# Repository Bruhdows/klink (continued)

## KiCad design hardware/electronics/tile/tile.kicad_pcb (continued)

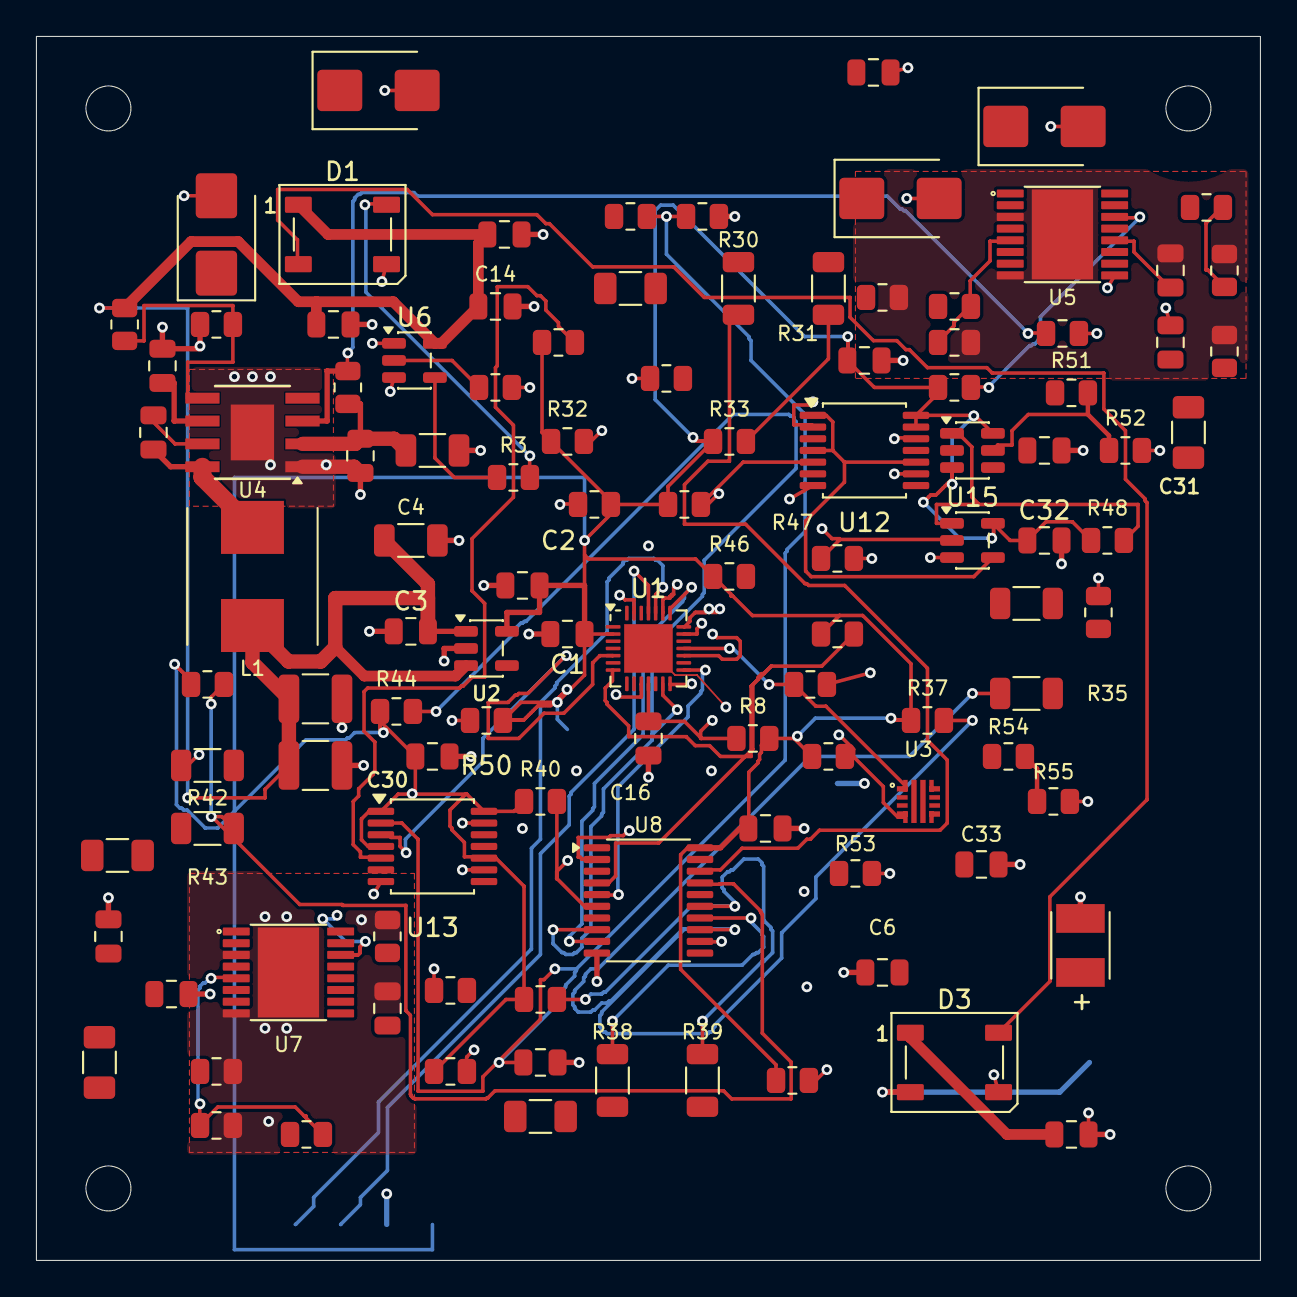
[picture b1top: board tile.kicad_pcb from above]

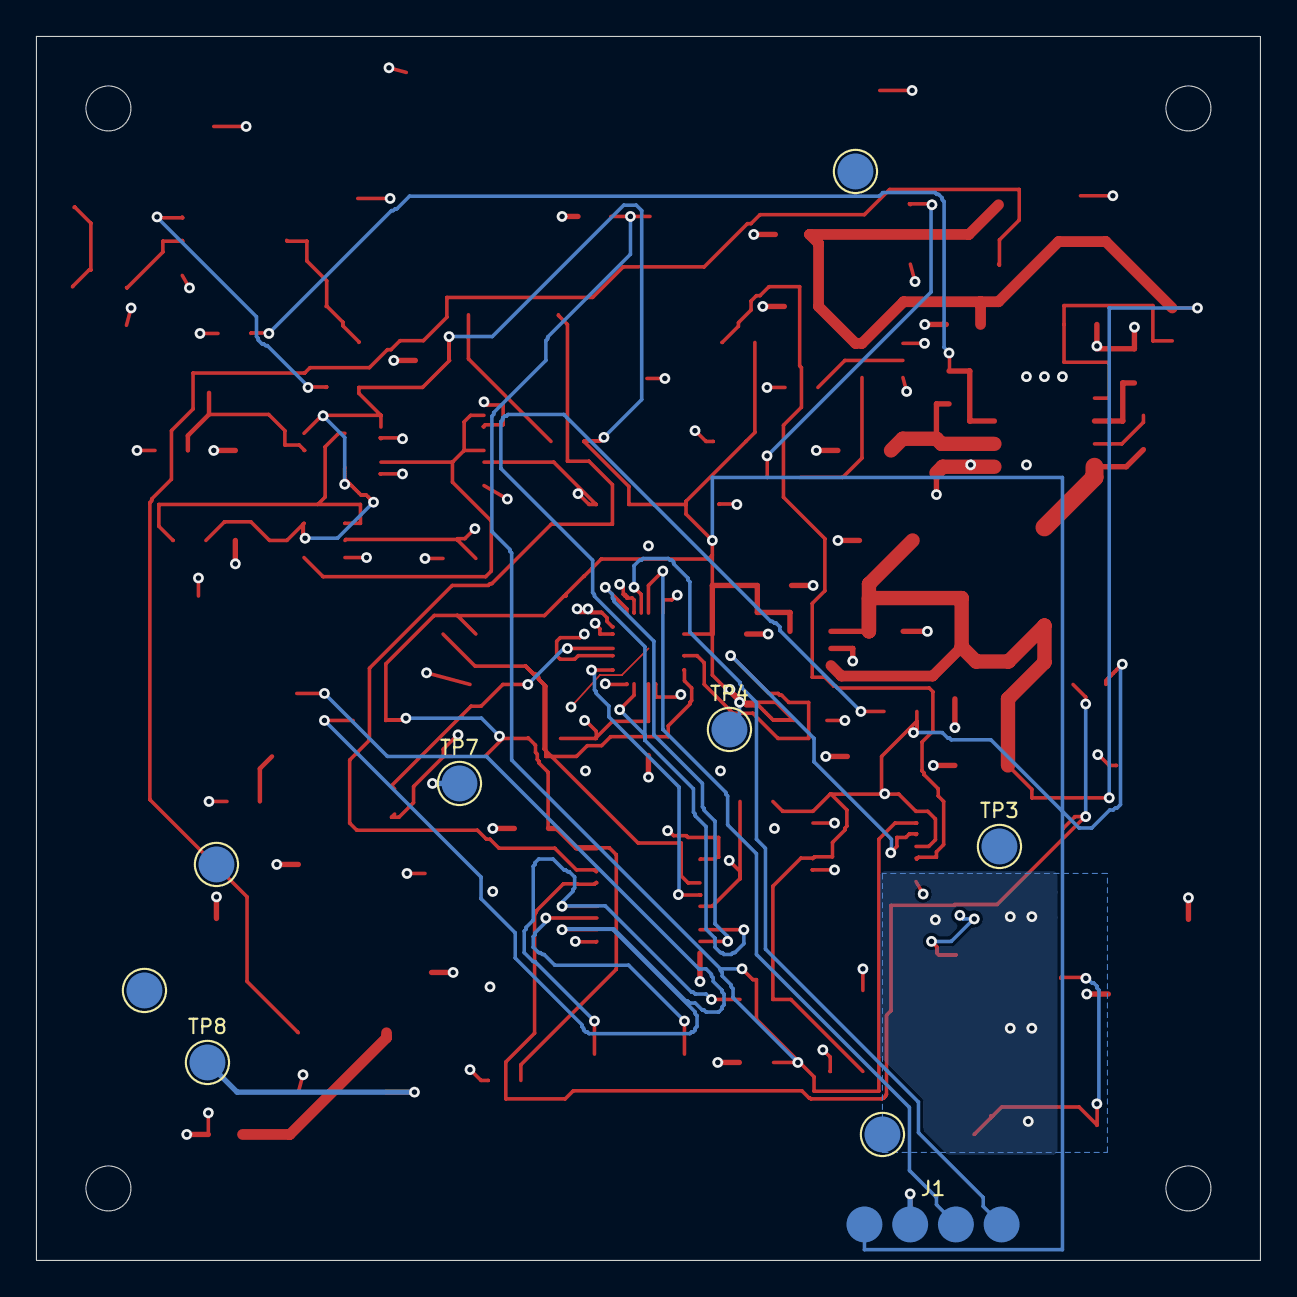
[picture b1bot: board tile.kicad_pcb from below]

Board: 4 copper layers, 68.0 x 68.0 mm, 122 parts (9 on the bottom side), 70 nets.

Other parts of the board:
H1, H2, H3, H4: MountingHole_2.5mm

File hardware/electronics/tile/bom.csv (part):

reference,value,manufacturer_part_number,lcsc_reference,qty_per_tile,qty_for_20_tiles,footprint,purchase_url,unit_price,currency,stock_status,verification_status,qty_for_16_tiles,qty_for_32_tiles,price_status,checked_date
C1,100nF 50V X7R,C2012X7R1H104K125AE,,1,20,Capacitor_SMD:C_0805_2012Metric,https://www.mouser.com/ProductDetail/TDK/C2012X7R1H104K125AE,0.1,USD,,manufacturer data selection; assembly and electrical qualification pending,16,32,engineering allowance; NOT a verified supplier price,
C2,4.7uF,C2012X7R1C475K125AB,,1,20,Capacitor_SMD:C_0805_2012Metric,https://www.mouser.com/ProductDetail/TDK/C2012X7R1C475K125AB,0.1,USD,,manufacturer data selection; assembly and electrical qualification pending,16,32,engineering allowance; NOT a verified supplier price,
C3,1uF,C2012X7R1H105K125AB,,1,20,Capacitor_SMD:C_0805_2012Metric,https://www.mouser.com/ProductDetail/TDK/C2012X7R1H105K125AB,0.1,USD,,manufacturer data selection; assembly and electrical qualification pending,16,32,engineering allowance; NOT a verified supplier price,
C4,10µF,C3216X7R1C106K160AC,,1,20,Capacitor_SMD:C_1206_3216Metric,https://www.mouser.com/ProductDetail/TDK/C3216X7R1C106K160AC,0.35,USD,,manufacturer data selection; assembly and electrical qualification pending,16,32,engineering allowance; NOT a verified supplier price,
C5,100nF 50V X7R,C2012X7R1H104K125AE,,1,20,Capacitor_SMD:C_0805_2012Metric,https://www.mouser.com/ProductDetail/TDK/C2012X7R1H104K125AE,0.1,USD,,manufacturer data selection; assembly and electrical qualification pending,16,32,engineering allowance; NOT a verified supplier price,
C6,100nF 50V X7R,C2012X7R1H104K125AE,,1,20,Capacitor_SMD:C_0805_2012Metric,https://www.mouser.com/ProductDetail/TDK/C2012X7R1H104K125AE,0.1,USD,,manufacturer data selection; assembly and electrical qualification pending,16,32,engineering allowance; NOT a verified supplier price,
C7,120uF 6.3V,6TPE120MAZB,,1,20,Klink:CP_Panasonic_POSCAP_B2,https://www.mouser.com/ProductDetail/Panasonic/6TPE120MAZB,1.2,USD,not procurement-confirmed,datasheet-reviewed design selection; physical qualification pending; do not use above 85C at full 5V-rail tolerance,16,32,engineering allowance; NOT a verified supplier price,
C8,10uF 50V X7R,C3216X7R1H106K160AC,,1,20,Capacitor_SMD:C_1206_3216Metric,https://www.mouser.com/ProductDetail/TDK/C3216X7R1H106K160AC,0.35,USD,,manufacturer data selection; assembly and electrical qualification pending,16,32,engineering allowance; NOT a verified supplier price,
C9,100nF 50V X7R,C2012X7R1H104K125AE,,1,20,Capacitor_SMD:C_0805_2012Metric,https://www.mouser.com/ProductDetail/TDK/C2012X7R1H104K125AE,0.1,USD,,manufacturer data selection; assembly and electrical qualification pending,16,32,engineering allowance; NOT a verified supplier price,
C10,100nF 50V X7R,C2012X7R1H104K125AE,,1,20,Capacitor_SMD:C_0805_2012Metric,https://www.mouser.com/ProductDetail/TDK/C2012X7R1H104K125AE,0.1,USD,,manufacturer data selection; assembly and electrical qualification pending,16,32,engineering allowance; NOT a verified supplier price,
C11,22uF 25V X7R,C1210C226K3RACTU,,1,20,Capacitor_SMD:C_1210_3225Metric,https://www.mouser.com/ProductDetail/KEMET/C1210C226K3RACTU,0.35,USD,,manufacturer data selection; assembly and electrical qualification pending,16,32,engineering allowance; NOT a verified supplier price,
C12,22uF 25V X7R,C1210C226K3RACTU,,1,20,Capacitor_SMD:C_1210_3225Metric,https://www.mouser.com/ProductDetail/KEMET/C1210C226K3RACTU,0.35,USD,,manufacturer data selection; assembly and electrical qualification pending,16,32,engineering allowance; NOT a verified supplier price,
C13,10nF 50V,CC0805KRX7R9BB103,,1,20,Capacitor_SMD:C_0805_2012Metric,https://www.mouser.com/ProductDetail/Yageo/CC0805KRX7R9BB103,0.1,USD,,manufacturer data selection; assembly and electrical qualification pending,16,32,engineering allowance; NOT a verified supplier price,
C14,100nF 50V X7R,C2012X7R1H104K125AE,,1,20,Capacitor_SMD:C_0805_2012Metric,https://www.mouser.com/ProductDetail/TDK/C2012X7R1H104K125AE,0.1,USD,,manufacturer data selection; assembly and electrical qualification pending,16,32,engineering allowance; NOT a verified supplier price,
C15,100nF 50V X7R,C2012X7R1H104K125AE,,1,20,Capacitor_SMD:C_0805_2012Metric,https://www.mouser.com/ProductDetail/TDK/C2012X7R1H104K125AE,0.1,USD,,manufacturer data selection; assembly and electrical qualification pending,16,32,engineering allowance; NOT a verified supplier price,
C16,10nF,CC0805KRX7R9BB103,,1,20,Capacitor_SMD:C_0805_2012Metric,https://www.mouser.com/ProductDetail/Yageo/CC0805KRX7R9BB103,0.1,USD,,manufacturer data selection; assembly and electrical qualification pending,16,32,engineering allowance; NOT a verified supplier price,
C17,100nF 50V X7R,C2012X7R1H104K125AE,,1,20,Capacitor_SMD:C_0805_2012Metric,https://www.mouser.com/ProductDetail/TDK/C2012X7R1H104K125AE,0.1,USD,,manufacturer data selection; assembly and electrical qualification pending,16,32,engineering allowance; NOT a verified supplier price,
C18,1uF 50V,C2012X7R1H105K125AB,,1,20,Capacitor_SMD:C_0805_2012Metric,https://www.mouser.com/ProductDetail/TDK/C2012X7R1H105K125AB,0.1,USD,,manufacturer data selection; assembly and electrical qualification pending,16,32,engineering allowance; NOT a verified supplier price,
C19,1uF 50V,C2012X7R1H105K125AB,,1,20,Capacitor_SMD:C_0805_2012Metric,https://www.mouser.com/ProductDetail/TDK/C2012X7R1H105K125AB,0.1,USD,,manufacturer data selection; assembly and electrical qualification pending,16,32,engineering allowance; NOT a verified supplier price,
C20,100nF 50V X7R,C2012X7R1H104K125AE,,1,20,Capacitor_SMD:C_0805_2012Metric,https://www.mouser.com/ProductDetail/TDK/C2012X7R1H104K125AE,0.1,USD,,manufacturer data selection; assembly and electrical qualification pending,16,32,engineering allowance; NOT a verified supplier price,
C33,10nF 50V,CC0805KRX7R9BB103,,1,20,Capacitor_SMD:C_0805_2012Metric,https://www.mouser.com/ProductDetail/Yageo/CC0805KRX7R9BB103,0.1,USD,,manufacturer data selection; assembly and electrical qualification pending,16,32,engineering allowance; NOT a verified supplier price,
D1,WS2812B-V5,WS2812B-V5,C2846931,1,20,LED_SMD:LED_WS2812B_PLCC4_5.0x5.0mm_P3.2mm,https://www.mouser.com/ProductDetail/Worldsemi/WS2812B-V5,0.18,USD,not procurement-confirmed,datasheet-reviewed design selection; physical qualification pending; actual LED variant not confirmed,16,32,engineering allowance; NOT a verified supplier price,
D3,WS2812B-V5,WS2812B-V5,C2846931,1,20,LED_SMD:LED_WS2812B_PLCC4_5.0x5.0mm_P3.2mm,https://www.mouser.com/ProductDetail/Worldsemi/WS2812B-V5,0.18,USD,not procurement-confirmed,datasheet-reviewed design selection; physical qualification pending; actual LED variant not confirmed,16,32,engineering allowance; NOT a verified supplier price,
J1,DEBUG_3V3_MONITOR,,,0,0,Klink:Debug_1x04_P2.54_Pads,,,,not procurement-confirmed,bare copper; no purchased component,0,0,,
J2,DNP_FACTORY_BUS_TEST,,,0,0,,,,,not procurement-confirmed,DNP factory schematic access; excluded from board,0,0,,
J3,EDGE_5P_TBD,,,1,20,,,,,not procurement-confirmed,preferred sample candidate SAMZO 03E315320 / C42402947; NOT selected production MPN; stroke/current/plating/land width unresolved; no production footprint assigned,16,32,,
J4,EDGE_5P_TBD,,,1,20,,,,,not procurement-confirmed,flat mating face candidate; carrier/finish/numbering not released; no production footprint assigned,16,32,,
J5,EDGE_5P_TBD,,,1,20,,,,,not procurement-confirmed,flat mating face candidate; carrier/finish/numbering not released; no production footprint assigned,16,32,,
J6,EDGE_5P_TBD,,,1,20,,,,,not procurement-confirmed,preferred sample candidate SAMZO 03E315320 / C42402947; NOT selected production MPN; stroke/current/plating/land width unresolved; no production footprint assigned,16,32,,
J7,Conn_01x08,,,1,20,,,,,not procurement-confirmed,connector geometry/part not released; no footprint assigned,16,32,,
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
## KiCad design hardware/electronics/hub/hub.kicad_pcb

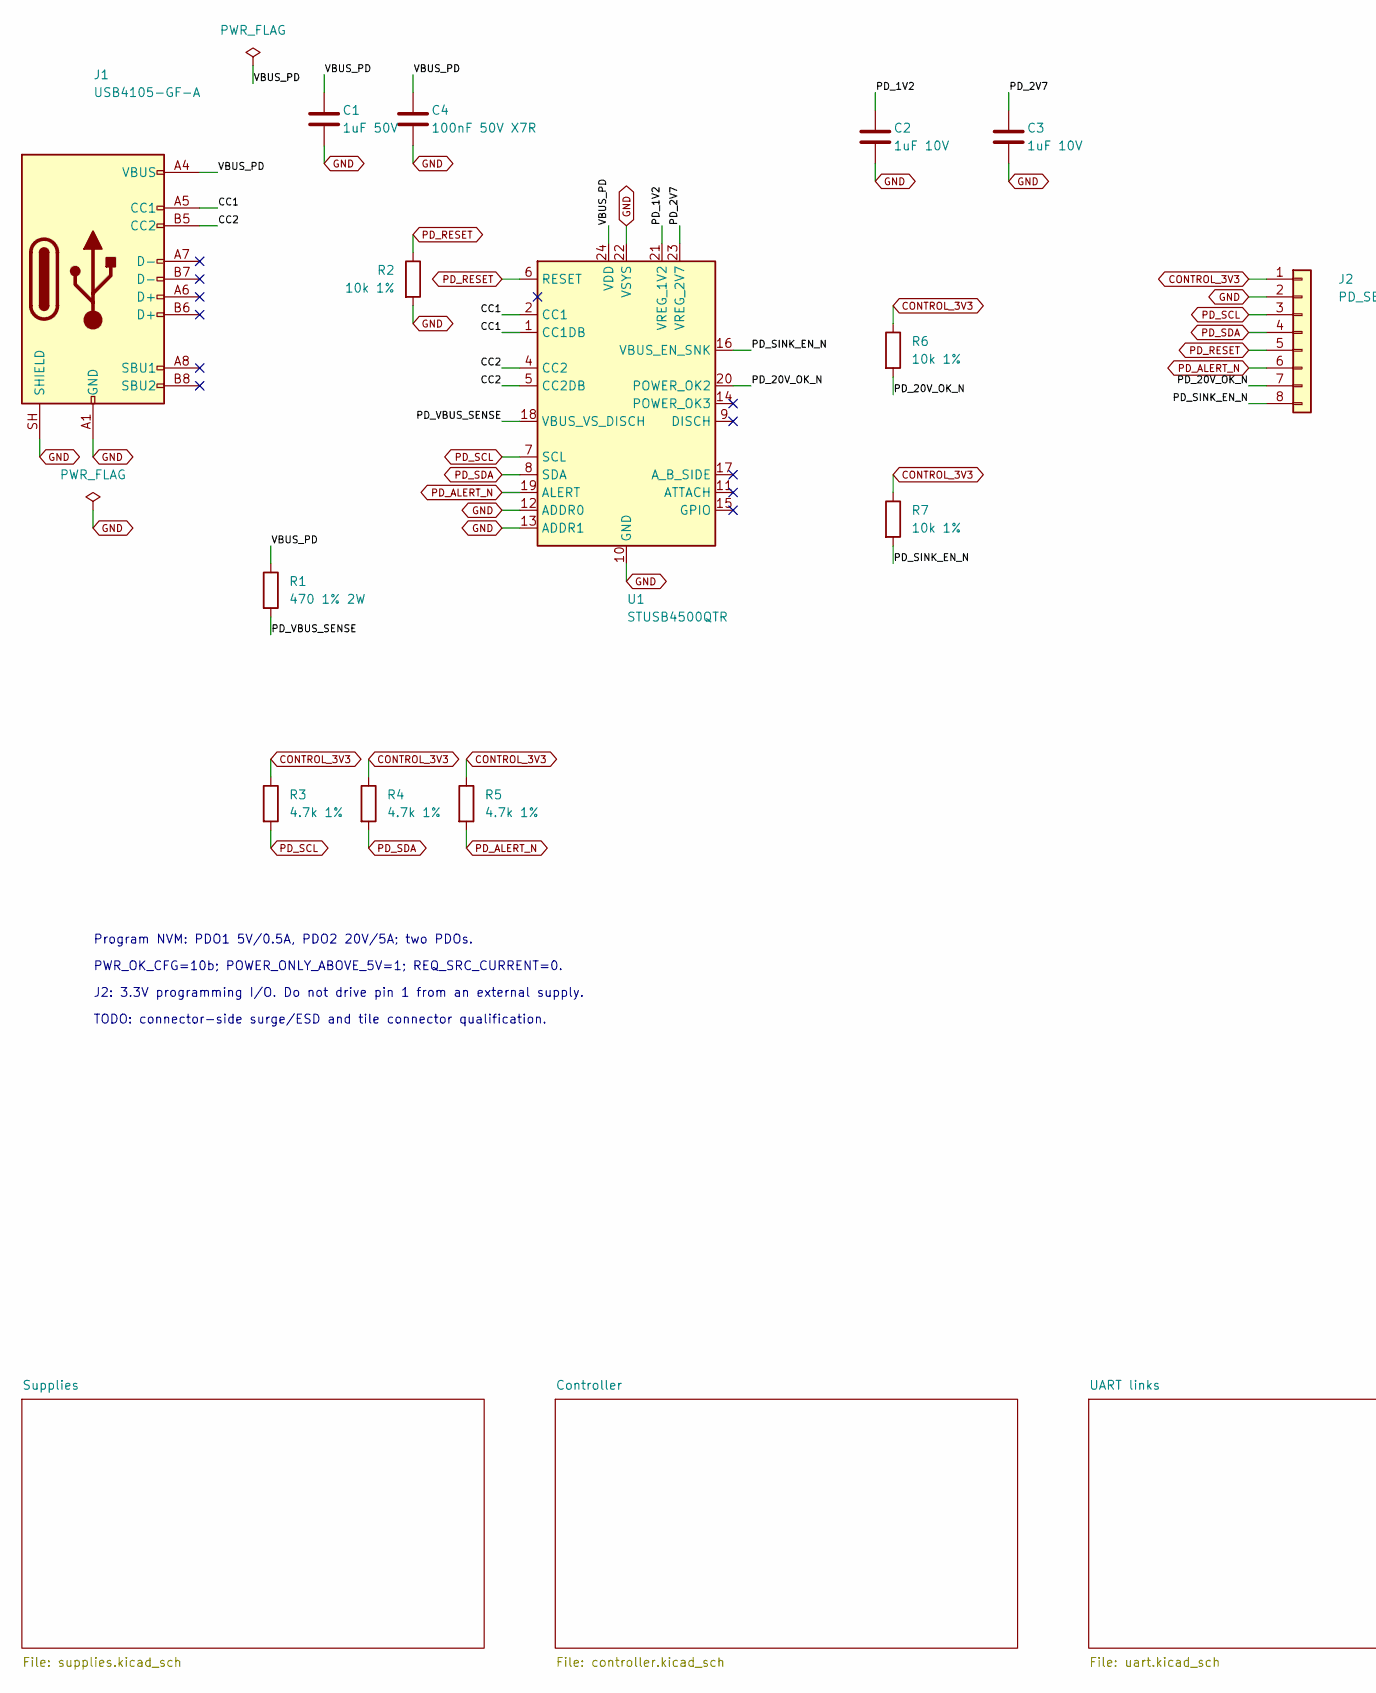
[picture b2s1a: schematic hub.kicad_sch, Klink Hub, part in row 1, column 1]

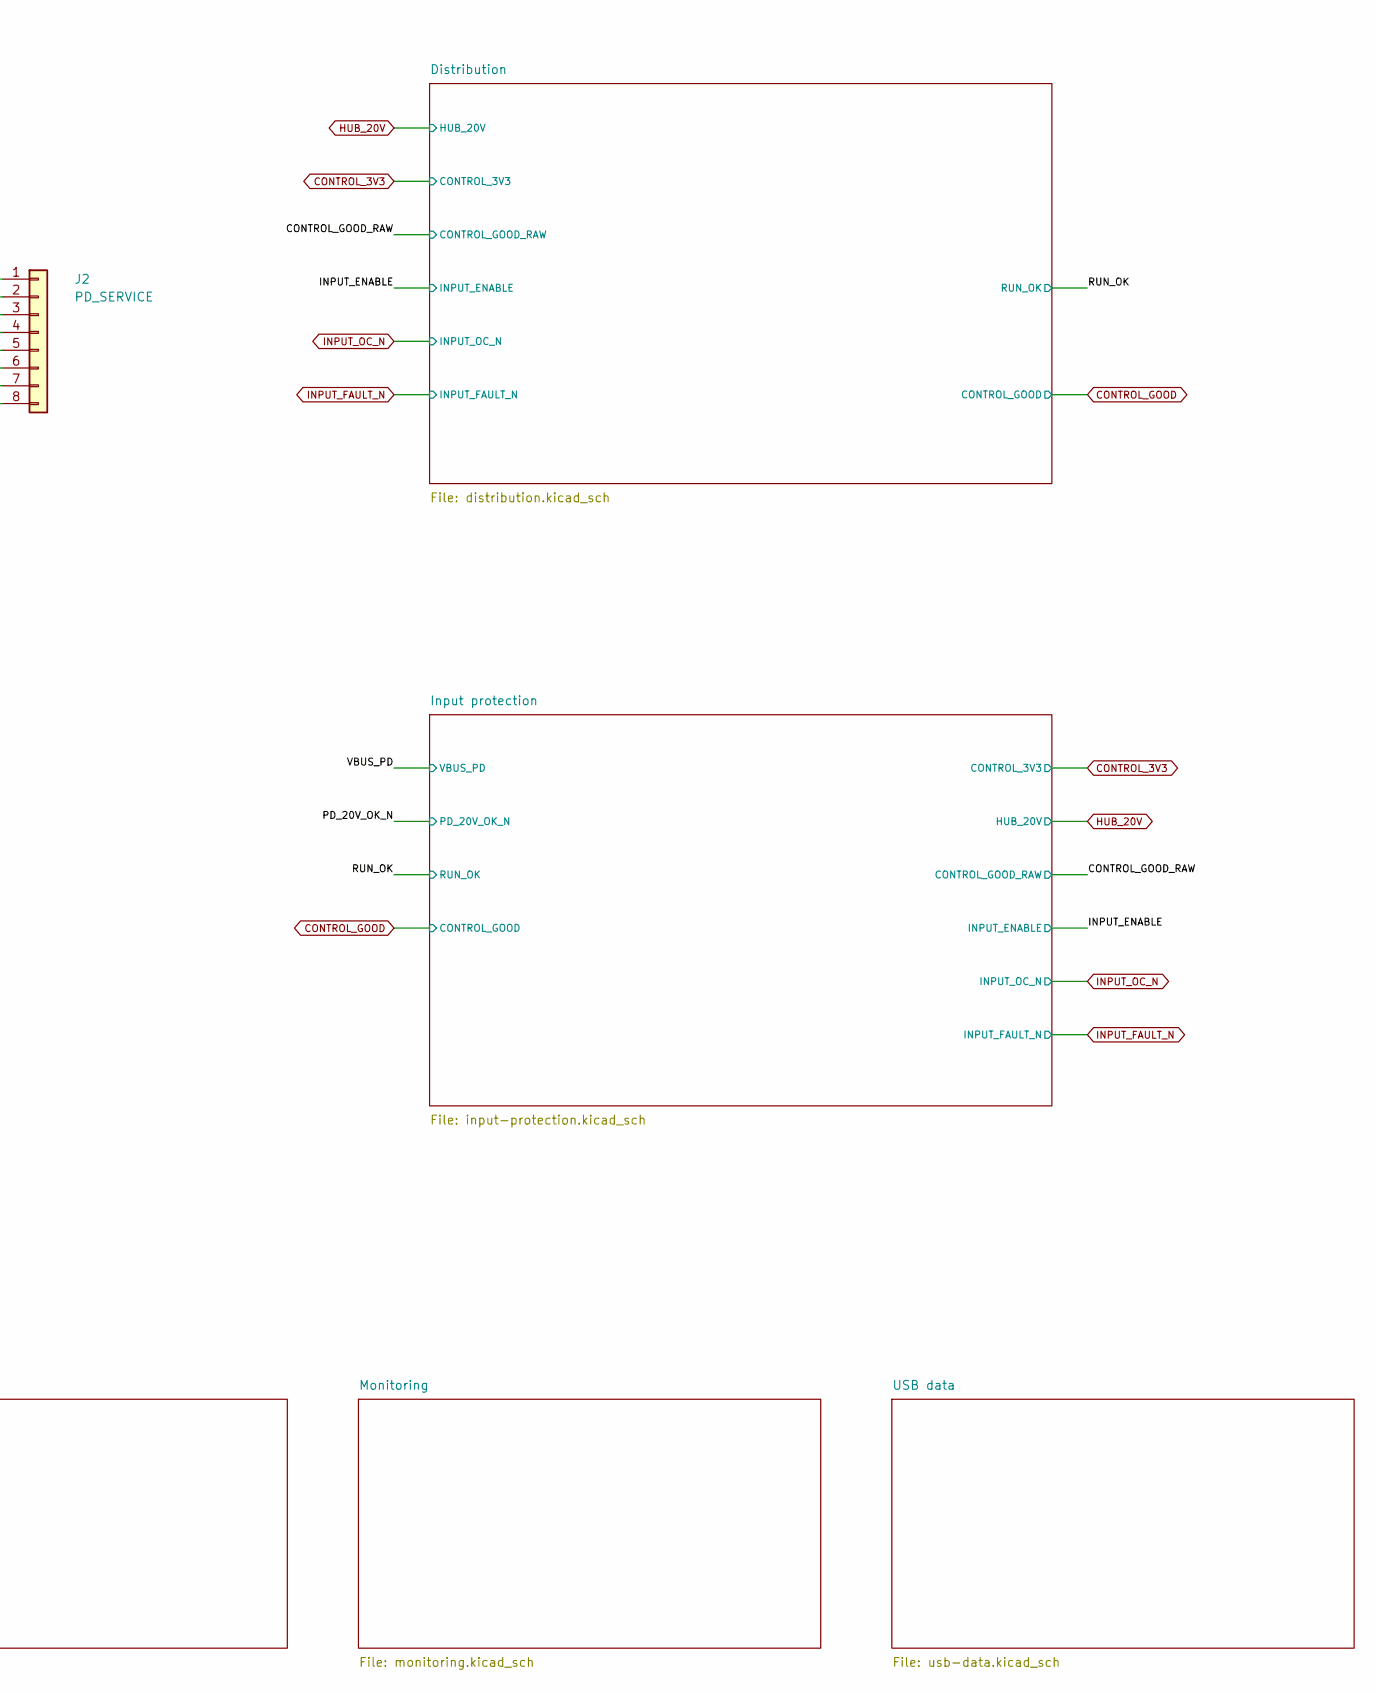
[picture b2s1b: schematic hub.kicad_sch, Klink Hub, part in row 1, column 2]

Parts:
C1: 1uF 50V; C_0805_2012Metric; MPN C2012X7R1H105K125AB
C2, C3: 1uF 10V; C_0805_2012Metric; MPN C2012X7R1H105K125AB
C4: 100nF 50V X7R; C_0805_2012Metric; MPN C2012X7R1H104K125AE
J1: USB4105-GF-A; USB_C_Receptacle_GCT_USB4105_RoundedGround; MPN USB4105-GF-A
J2: PD_SERVICE; PinHeader_1x08_P2.54mm_Vertical; MPN TSW-108-07-G-S
R1: 470 1% 2W; R_2512_6332Metric; MPN RC2512FK-7W470RL
R2, R6, R7: 10k 1%; R_0805_2012Metric; MPN RC0805FR-0710KL
R3, R4, R5: 4.7k 1%; R_0805_2012Metric; MPN RC0805FR-074K7L
U1: STUSB4500QTR; QFN-24-1EP_4x4mm_P0.5mm_EP2.7x2.7mm; MPN STUSB4500QTR

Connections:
/CC1: J1.A5 (CC1), U1.1 (CC1DB), U1.2 (CC1)
/CC2: J1.B5 (CC2), U1.4 (CC2), U1.5 (CC2DB)
/PD_1V2: C2.1, U1.21 (VREG_1V2)
/PD_2V7: C3.1, U1.23 (VREG_2V7)
/PD_20V_OK_N: J2.7, R6.2, U1.20 (POWER_OK2); also elsewhere on the board
/PD_SINK_EN_N: J2.8, R7.2, U1.16 (VBUS_EN_SNK)
/PD_VBUS_SENSE: R1.2, U1.18 (VBUS_VS_DISCH)
/VBUS_PD: C1.1, C4.1, J1.A4 (VBUS), J1.A9 (VBUS), J1.B4 (VBUS), J1.B9 (VBUS), R1.1, U1.24 (VDD); also elsewhere on the board
CONTROL_3V3: J2.1, R3.1, R4.1, R5.1, R6.1, R7.1; also elsewhere on the board
GND: C1.2, C2.2, C3.2, C4.2, J1.A1 (GND), J1.A12 (GND), J1.B1 (GND), J1.B12 (GND), J1.SH (SHIELD), J2.2, R2.2, U1.10 (GND), U1.12 (ADDR0), U1.13 (ADDR1), U1.22 (VSYS), U1.25 (GND); also elsewhere on the board
PD_ALERT_N: J2.6, R5.2, U1.19 (ALERT); also elsewhere on the board
PD_RESET: J2.5, R2.1, U1.6 (RESET); also elsewhere on the board
PD_SCL: J2.3, R3.2, U1.7 (SCL); also elsewhere on the board
PD_SDA: J2.4, R4.2, U1.8 (SDA); also elsewhere on the board

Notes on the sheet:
Program NVM: PDO1 5V/0.5A, PDO2 20V/5A; two PDOs.
PWR_OK_CFG=10b; POWER_ONLY_ABOVE_5V=1; REQ_SRC_CURRENT=0.
J2: 3.3V programming I/O. Do not drive pin 1 from an external supply.
TODO: connector-side surge/ESD and tile connector qualification.

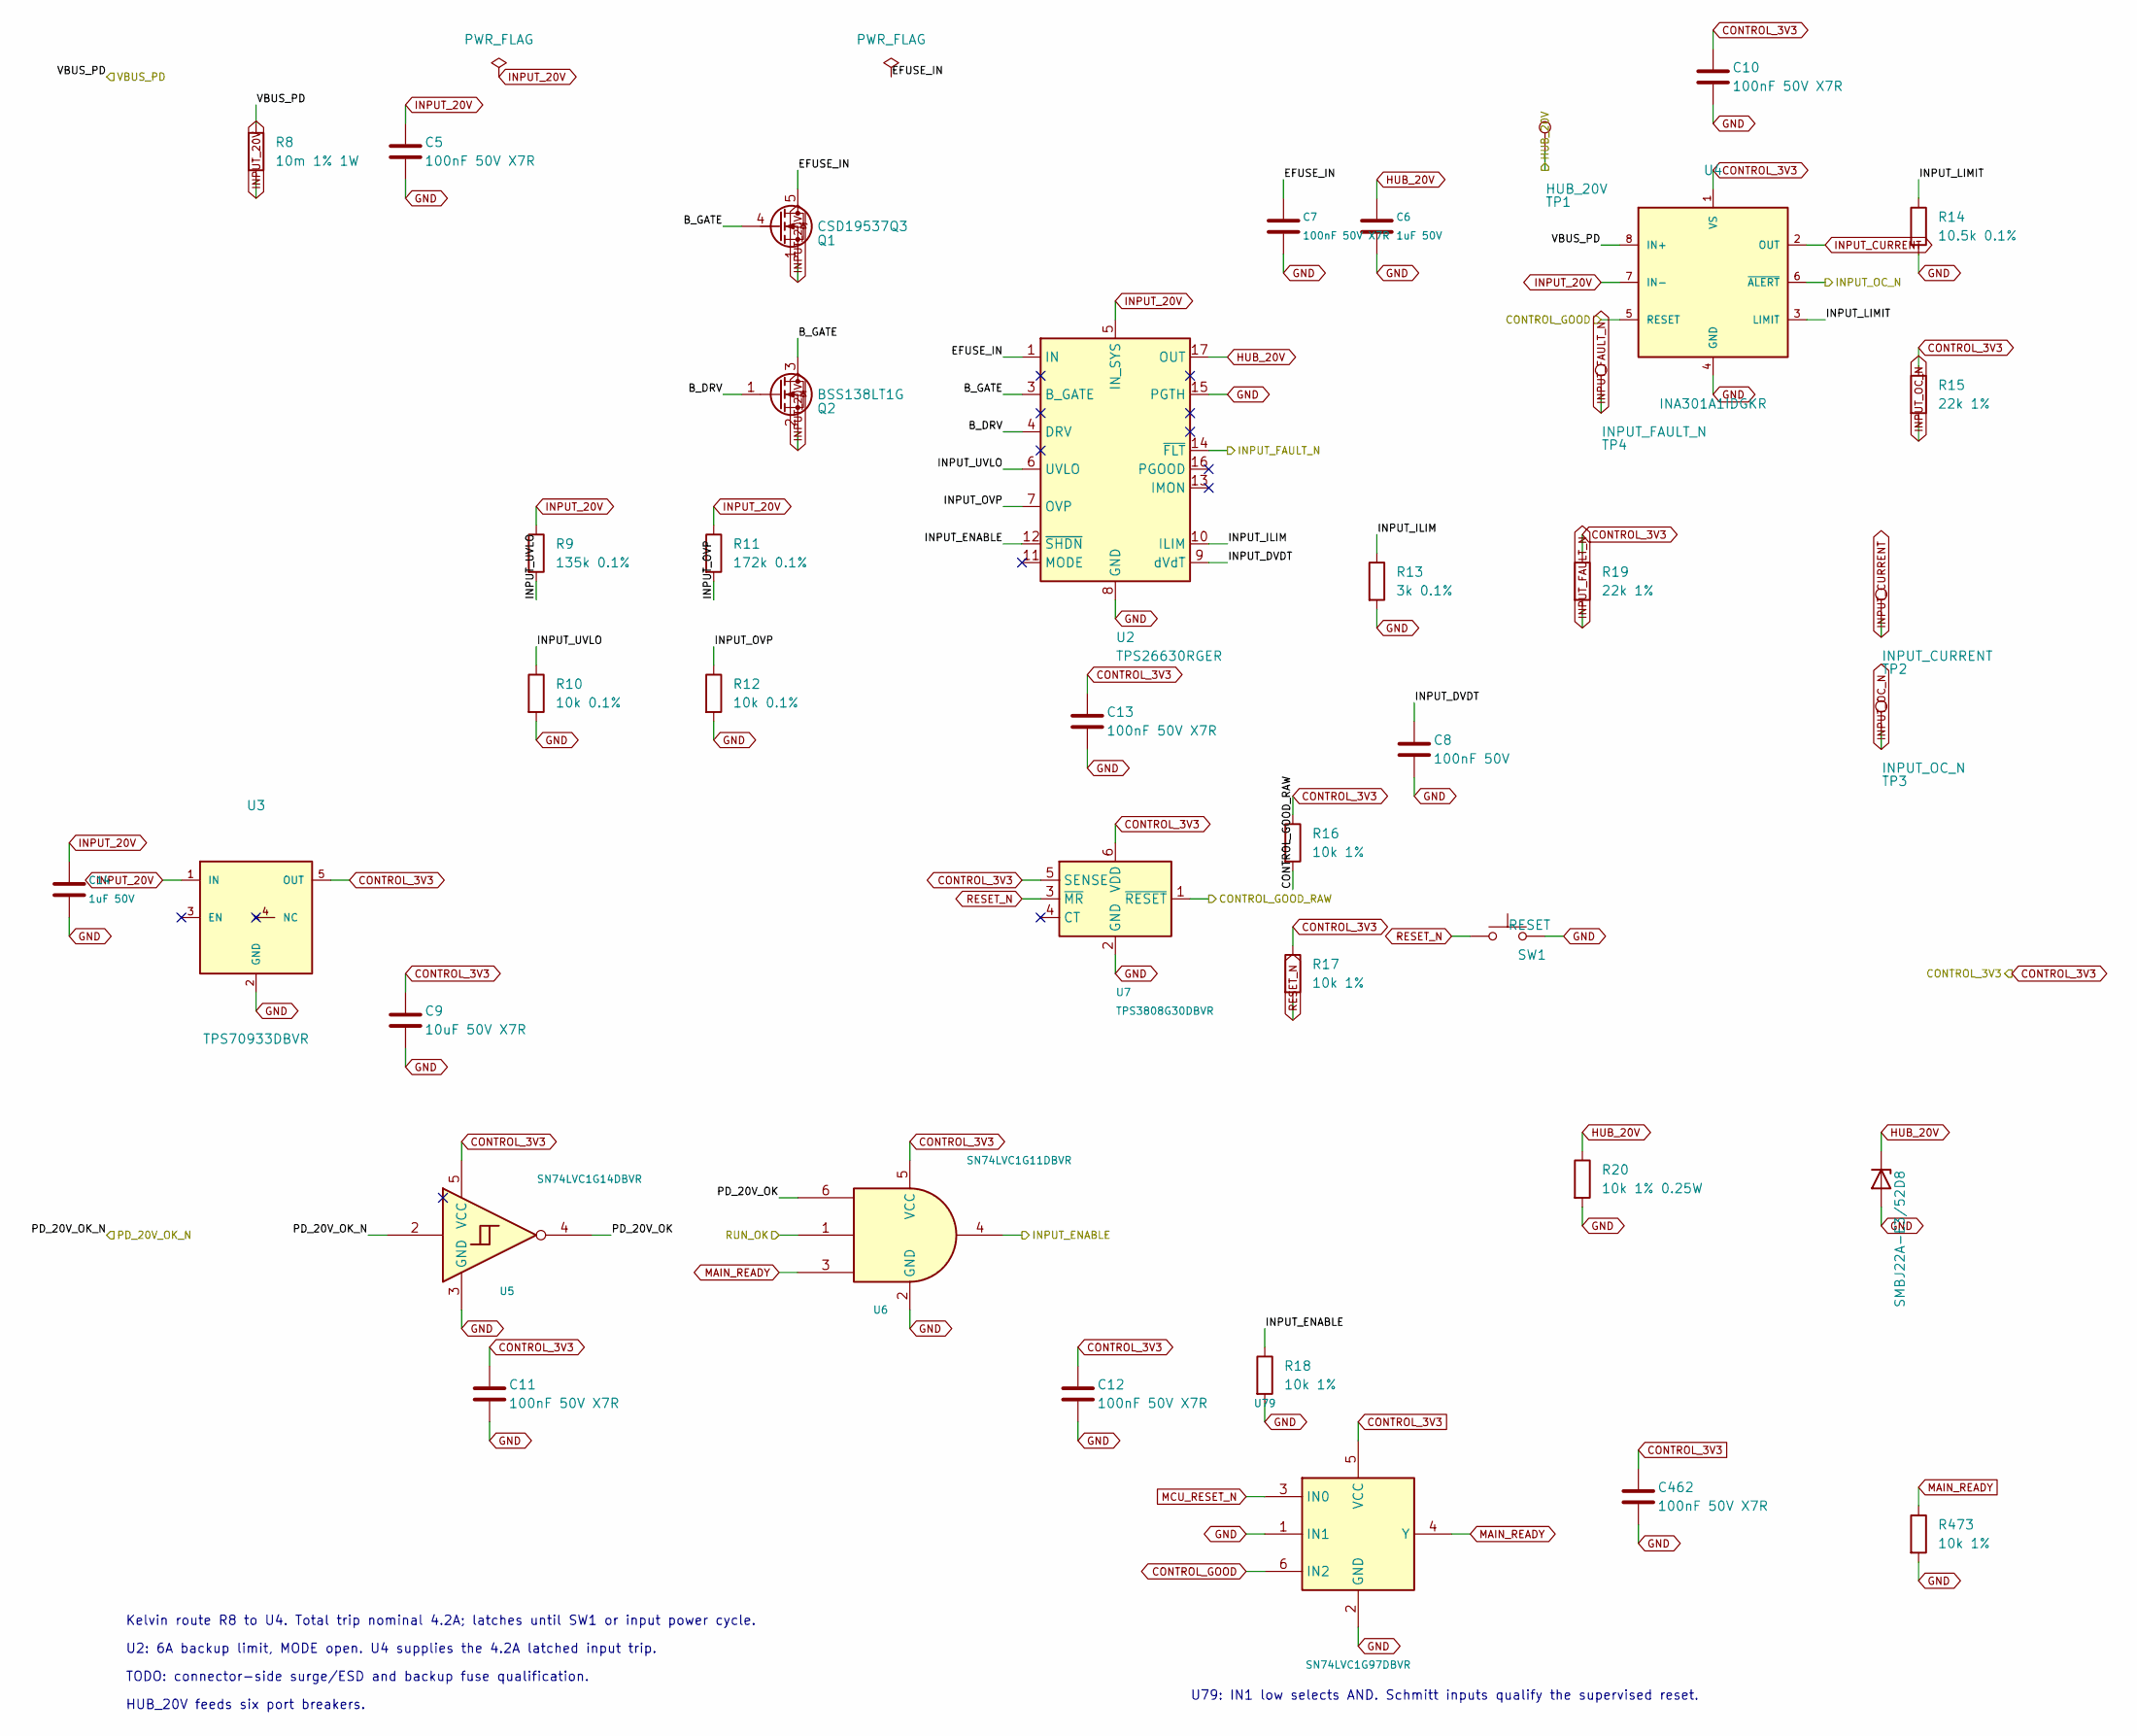
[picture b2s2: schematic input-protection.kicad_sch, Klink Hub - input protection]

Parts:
C5, C7, C10, C11, C12, C13, C462: 100nF 50V X7R; C_0805_2012Metric; MPN C2012X7R1H104K125AE
C6, C14: 1uF 50V; C_0805_2012Metric; MPN C2012X7R1H105K125AB
C8: 100nF 50V; C_0805_2012Metric; MPN C2012X7R1H104K125AE
C9: 10uF 50V X7R; C_1206_3216Metric; MPN C3216X7R1H106K160AC
D8: SMBJ22A-E3/52; D_SMB; MPN SMBJ22A-E3/52
Q1: CSD19537Q3; CSD19537Q3_TI; MPN CSD19537Q3
Q2: BSS138LT1G; SOT-23; MPN BSS138LT1G
R8: 10m 1% 1W; R_Vishay_WSL2512_10m; MPN WSL2512R0100FEA
R9: 135k 0.1%; R_0805_2012Metric; MPN TNPW0805135KBEEA
R10, R12: 10k 0.1%; R_0805_2012Metric; MPN TNPW080510K0BEEA
R11: 172k 0.1%; R_0805_2012Metric; MPN TNPW0805172KBEEA
R13: 3k 0.1%; R_0805_2012Metric; MPN TNPW08053K00BEEA
R14: 10.5k 0.1%; R_0805_2012Metric; MPN ERA6AEB1052V
R15, R19: 22k 1%; R_0805_2012Metric; MPN RC0805FR-0722KL
R16, R17, R18, R473: 10k 1%; R_0805_2012Metric; MPN RC0805FR-0710KL
R20: 10k 1% 0.25W; R_1206_3216Metric; MPN RC1206FR0710KL
SW1: RESET; SW_SPST_B3U-1000P; MPN B3U-1000P
TP1: HUB_20V; TestPoint_Pad_D2.0mm
TP2: INPUT_CURRENT; TestPoint_Pad_D2.0mm
TP3: INPUT_OC_N; TestPoint_Pad_D2.0mm
TP4: INPUT_FAULT_N; TestPoint_Pad_D2.0mm
U2: TPS26630RGER; Texas_RGE0024H_VQFN-24-1EP_4x4mm_P0.5mm_EP2.7x2.7mm_Thermal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; MPN TPS26630RGER
U3: TPS70933DBVR; SOT-23-5; MPN TPS70933DBVR
U4: INA301A1IDGKR; VSSOP-8_3x3mm_P0.65mm; MPN INA301A1IDGKR
U5: SN74LVC1G14DBVR; SOT-23-5; MPN SN74LVC1G14DBVR
U6: SN74LVC1G11DBVR; SOT-23-6; MPN SN74LVC1G11DBVR
U7: TPS3808G30DBVR; SOT-23-6; MPN TPS3808G30DBVR
U79: SN74LVC1G97DBVR; SOT-23-6; MPN SN74LVC1G97DBVR

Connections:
/CONTROL_GOOD_RAW: R16.2, U7.1 (~RESET); also elsewhere on the board
/INPUT_ENABLE: R18.1, U2.12 (~SHDN), U6.4; also elsewhere on the board
/Input protection/B_DRV: Q2.1 (G), U2.4 (DRV)
/Input protection/B_GATE: Q1.4 (G), Q2.3 (D), U2.3 (B_GATE)
/Input protection/EFUSE_IN: C7.1, Q1.5 (D), U2.1 (IN), U2.2 (IN)
/Input protection/INPUT_DVDT: C8.1, U2.9 (dVdT)
/Input protection/INPUT_ILIM: R13.1, U2.10 (ILIM)
/Input protection/INPUT_LIMIT: R14.1, U4.3 (LIMIT)
/Input protection/INPUT_OVP: R11.2, R12.1, U2.7 (OVP)
/Input protection/INPUT_UVLO: R9.2, R10.1, U2.6 (UVLO)
/Input protection/PD_20V_OK: U5.4, U6.6
/PD_20V_OK_N: U5.2; also elsewhere on the board
/RUN_OK: U6.1; also elsewhere on the board
/VBUS_PD: R8.1, U4.8 (IN+); also elsewhere on the board
CONTROL_3V3: C9.1, C10.1, C11.1, C12.1, C13.1, C462.1, R15.1, R16.1, R17.1, R19.1, U3.5 (OUT), U4.1 (VS), U5.5 (VCC), U6.5 (VCC), U7.5 (SENSE), U7.6 (VDD), U79.5 (VCC); also elsewhere on the board
CONTROL_GOOD: U4.5 (RESET), U79.6 (IN2); also elsewhere on the board
GND: C5.2, C6.2, C7.2, C8.2, C9.2, C10.2, C11.2, C12.2, C13.2, C14.2, C462.2, D8.2 (A), R10.2, R12.2, R13.2, R14.2, R18.2, R20.2, R473.2, SW1.2, U2.8 (GND), U2.15 (PGTH), U2.25 (GND), U3.2 (GND), U4.4 (GND), U5.3 (GND), U6.2 (GND), U7.2 (GND), U79.1 (IN1), U79.2 (GND); also elsewhere on the board
HUB_20V: C6.1, D8.1 (K), R20.1, TP1.1, U2.17 (OUT), U2.18 (OUT); also elsewhere on the board
INPUT_20V: C5.1, C14.1, Q1.1 (S), Q1.2 (S), Q1.3 (S), Q2.2 (S), R8.2, R9.1, R11.1, U2.5 (IN_SYS), U3.1 (IN), U4.7 (IN-); also elsewhere on the board
INPUT_CURRENT: TP2.1, U4.2 (OUT); also elsewhere on the board
INPUT_FAULT_N: R19.2, TP4.1, U2.14 (~FLT); also elsewhere on the board
INPUT_OC_N: R15.2, TP3.1, U4.6 (~ALERT); also elsewhere on the board
MAIN_READY: R473.1, U6.3, U79.4 (Y); also elsewhere on the board
MCU_RESET_N: U79.3 (IN0); also elsewhere on the board
RESET_N: R17.2, SW1.1, U7.3 (~MR); also elsewhere on the board

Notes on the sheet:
Kelvin route R8 to U4. Total trip nominal 4.2A; latches until SW1 or input power cycle.
U2: 6A backup limit, MODE open. U4 supplies the 4.2A latched input trip.
TODO: connector-side surge/ESD and backup fuse qualification.
HUB_20V feeds six port breakers.
U79: IN1 low selects AND. Schmitt inputs qualify the supervised reset.
